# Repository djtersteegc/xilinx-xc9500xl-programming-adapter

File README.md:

# xilinx-xc9500xl-programming-adapter
Xilinx XC9500XL programming adapter, for PLCC44 and QFP44 to DIP44 sockets

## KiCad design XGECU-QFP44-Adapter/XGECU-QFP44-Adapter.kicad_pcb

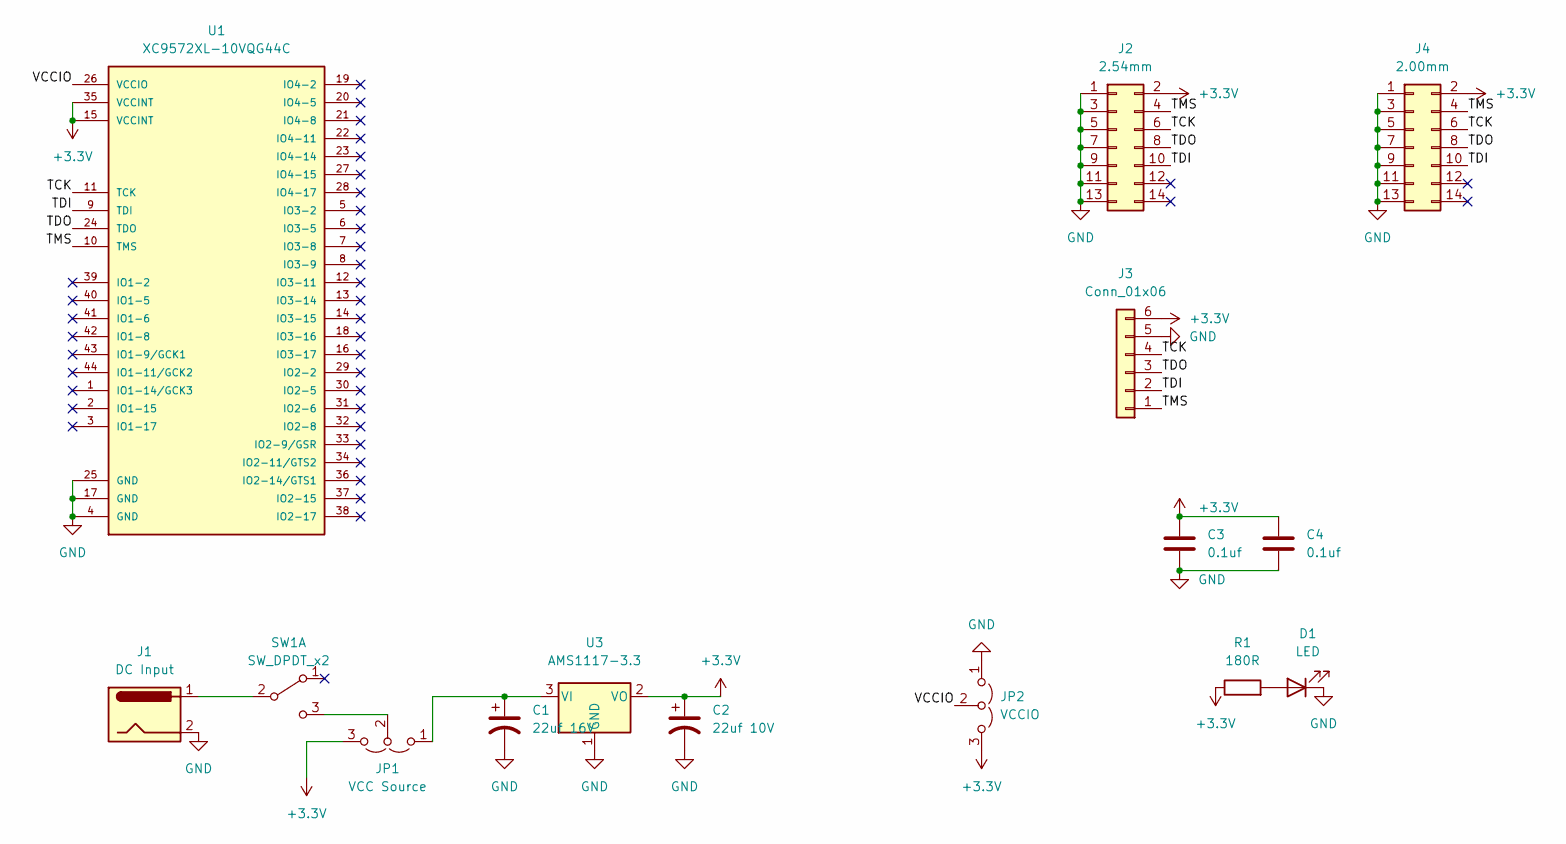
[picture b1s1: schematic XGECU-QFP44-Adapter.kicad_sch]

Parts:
C1: 22uf 16V; CP_EIA-3216-10_Kemet-I_Pad1.58x1.35mm_HandSolder
C2: 22uf 10V; CP_EIA-3216-10_Kemet-I_Pad1.58x1.35mm_HandSolder
C3, C4: 0.1uf; C_0805_2012Metric_Pad1.18x1.45mm_HandSolder
D1: LED; LED_D3.0mm
J1: DC Input; BarrelJack_Horizontal
J2: 2.54mm; IDC-Header_2x07_P2.54mm_Vertical
J3: Conn_01x06; PinHeader_1x06_P2.54mm_Horizontal
J4: 2.00mm; IDC-Header_2x07_P2.00mm_Vertical
JP1: VCC Source; PinHeader_1x03_P2.54mm_Vertical
JP2: VCCIO; PinHeader_1x03_P2.54mm_Vertical
R1: 180R; R_0805_2012Metric_Pad1.20x1.40mm_HandSolder
SW1: SW_DPDT_x2; KFC8.5x8.5 DPDT Push Switch
U1: XC9572XL-10VQG44C; XGECU-QFP44 to DIP44
U3: AMS1117-3.3; SOT-223-3_TabPin2

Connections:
+3.3V: C2.1, C3.1, C4.1, J2.2, J3.6, J4.2, JP1.3 (B), JP2.3 (B), R1.1, U1.15 (VCCINT), U1.35 (VCCINT), U3.2 (VO)
/TCK: J2.6, J3.4, J4.6, U1.11 (TCK)
/TDI: J2.10, J3.2, J4.10, U1.9 (TDI)
/TDO: J2.8, J3.3, J4.8, U1.24 (TDO)
/TMS: J2.4, J3.1, J4.4, U1.10 (TMS)
/VCCIO: JP2.2 (C), U1.26 (VCCIO)
GND: C1.2, C2.2, C3.2, C4.2, D1.1 (K), J1.2, J2.1, J2.3, J2.5, J2.7, J2.9, J2.11, J2.13, J3.5, J4.1, J4.3, J4.5, J4.7, J4.9, J4.11, J4.13, JP2.1 (A), U1.4 (GND), U1.17 (GND), U1.25 (GND), U3.1 (GND)
unnamed: D1.2 (A), R1.2
unnamed: C1.1, JP1.1 (A), U3.3 (VI)
unnamed: JP1.2 (C), SW1.3 (C)
unnamed: J1.1, SW1.2 (B)

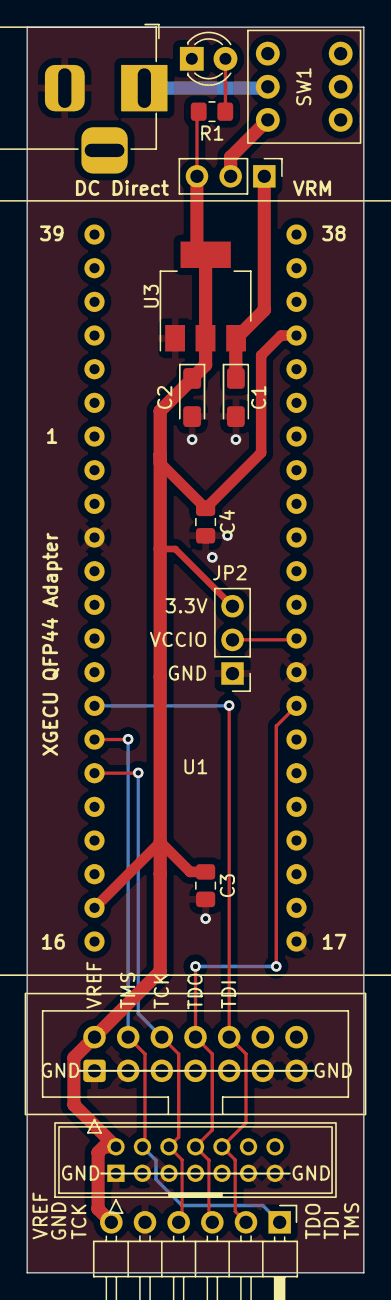
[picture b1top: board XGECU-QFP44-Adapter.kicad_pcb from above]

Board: 2 copper layers, 25.4 x 94.0 mm, 15 parts (0 on the bottom side), 11 nets.

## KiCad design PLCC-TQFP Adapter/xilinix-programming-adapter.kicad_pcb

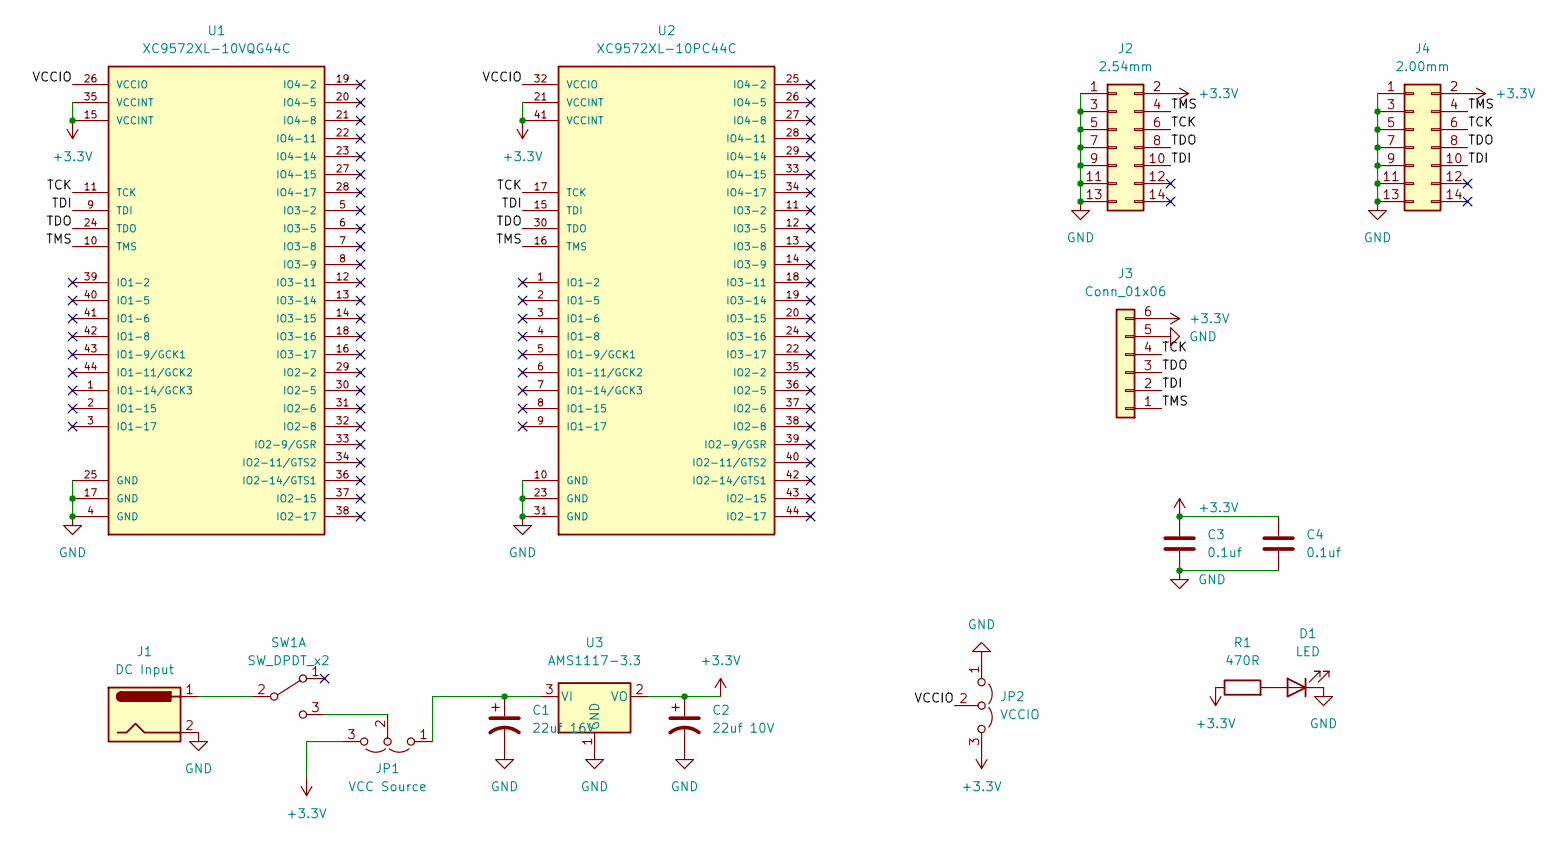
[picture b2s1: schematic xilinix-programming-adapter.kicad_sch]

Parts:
C1: 22uf 16V; CP_EIA-3216-10_Kemet-I_Pad1.58x1.35mm_HandSolder
C2: 22uf 10V; CP_EIA-3216-10_Kemet-I_Pad1.58x1.35mm_HandSolder
C3, C4: 0.1uf; C_0805_2012Metric_Pad1.18x1.45mm_HandSolder
D1: LED; LED_D3.0mm
J1: DC Input; BarrelJack_Horizontal
J2: 2.54mm; IDC-Header_2x07_P2.54mm_Vertical
J3: Conn_01x06; PinHeader_1x06_P2.54mm_Horizontal
J4: 2.00mm; IDC-Header_2x07_P2.00mm_Vertical
JP1: VCC Source; PinHeader_1x03_P2.54mm_Vertical
JP2: VCCIO; PinHeader_1x03_P2.54mm_Vertical
R1: 470R; R_0805_2012Metric_Pad1.20x1.40mm_HandSolder
SW1: SW_DPDT_x2; KFC8.5x8.5 DPDT Push Switch
U1: XC9572XL-10VQG44C; PLCC44-QFP44 to DIP44
U2: XC9572XL-10PC44C; PLCC44-QFP44 to DIP44
U3: AMS1117-3.3; SOT-223-3_TabPin2

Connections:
+3.3V: C2.1, C3.1, C4.1, J2.2, J3.6, J4.2, JP1.3 (B), JP2.3 (B), R1.1, U1.15 (VCCINT), U1.35 (VCCINT), U2.21 (VCCINT), U2.41 (VCCINT), U3.2 (VO); also elsewhere on the board
/TCK: J2.6, J3.4, J4.6, U1.11 (TCK), U2.17 (TCK)
/TDI: J2.10, J3.2, J4.10, U1.9 (TDI), U2.15 (TDI)
/TDO: J2.8, J3.3, J4.8, U1.24 (TDO), U2.30 (TDO)
/TMS: J2.4, J3.1, J4.4, U1.10 (TMS), U2.16 (TMS)
/VCCIO: JP2.2 (C), U1.26 (VCCIO), U2.32 (VCCIO); also elsewhere on the board
GND: C1.2, C2.2, C3.2, C4.2, D1.1 (K), J1.2, J2.1, J2.3, J2.5, J2.7, J2.9, J2.11, J2.13, J3.5, J4.1, J4.3, J4.5, J4.7, J4.9, J4.11, J4.13, JP2.1 (A), U1.4 (GND), U1.17 (GND), U1.25 (GND), U2.10 (GND), U2.23 (GND), U2.31 (GND), U3.1 (GND); also elsewhere on the board
unnamed: C1.1, JP1.1 (A), U3.3 (VI)
unnamed: D1.2 (A), R1.2
unnamed: J1.1, SW1.2 (B)
unnamed: JP1.2 (C), SW1.3 (C)

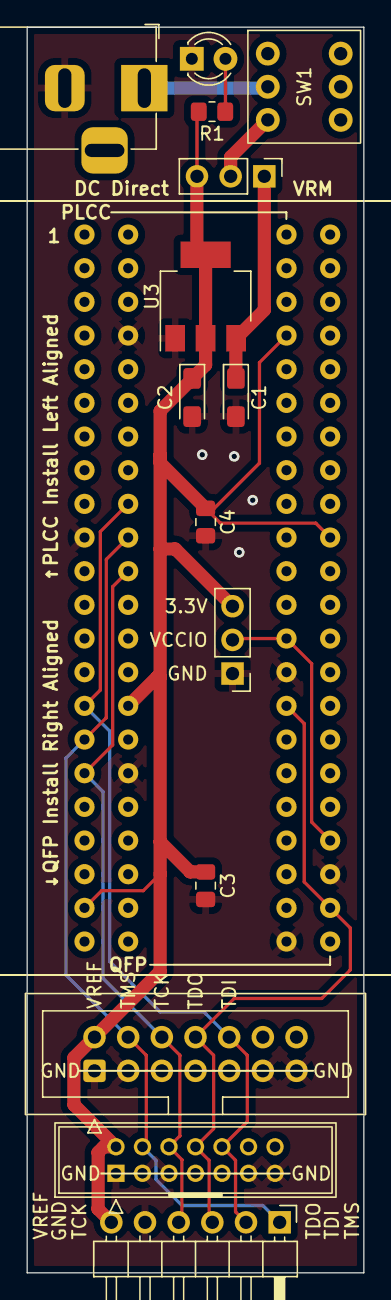
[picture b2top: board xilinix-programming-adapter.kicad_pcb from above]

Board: 2 copper layers, 25.4 x 94.0 mm, 16 parts (0 on the bottom side), 11 nets.

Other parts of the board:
VCCIO: VCCIO; PinHeader_1x03_P2.54mm_Vertical

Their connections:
+3.3V: VCCIO.3 (B); also elsewhere on the board
/VCCIO: VCCIO.2 (C); also elsewhere on the board
GND: VCCIO.1 (A); also elsewhere on the board

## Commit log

2025-03-14 V1.0
